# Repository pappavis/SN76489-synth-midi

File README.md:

Educatieve DIY USB-MIDI synthesizer gebaseerd op de SN76489 PSG,
aangestuurd via een ESP32-C2 met CircuitPython en een PCF8574
(I2C → parallel).

# Functionele specificaties  

## Ontwerpfilosofie
- Eerst breadboard, dan PCB
- Alles meetbaar met scope en multimeter
- Geen SMD-componenten
- Focus op leerbaarheid en reproduceerbaarheid

## Signaalpad (verplicht)
ESP32-C2 (USB MIDI)
→ PCF8574
→ SN76489
→ analoge filtering
→ variabel mono volume
→ audio-versterker
→ 3.5 mm TRS koptelefoon (dual-mono)

## Projectstatus
- [x] Stap 1 – Functionele specificaties
- [ ] Stap 2 – Technische specificaties
- [ ] Stap 3 – Blokdiagram
- [ ] Stap 4 – Breadboard ontwerp
- [ ] Stap 5 – Audio-versterker evaluatie
- [ ] Stap 6 – KiCad schema & PCB
- [ ] Stap 7 – Firmware architectuur
- [ ] Stap 8 – Test & debug
- [ ] Stap 9 – Verbeteringen

➡️ Begin bij `docs/01-functional-spec.md`
sn76489-midi-synth/
├── README.md
├── docs/
│   ├── 01-functional-spec.md
│   ├── 02-technical-spec.md
│   ├── 03-block-diagram.md
│   ├── 04-breadboard-design.md
│   ├── 05-audio-options-evaluation.md
│   ├── 06-kicad-design.md
│   ├── 07-firmware-architecture.md
│   ├── 08-test-and-debug.md
│   └── 09-improvements-and-next-steps.md
├── hardware/
│   ├── breadboard/
│   └── pcb/
├── firmware/
│   ├── circuitpython/
│   └── tools/
└── media/
    ├── photos/
    └── scope-captures/

# Werk-in-uitvoering

## Functioneel schema

## Printplaat klaar voor China-produtie

# CREDITS
In een opwelling gemaakt op een koude Zaterdagmiddag.

Michiel Erasmus

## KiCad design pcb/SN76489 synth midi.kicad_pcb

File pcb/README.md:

# Werk-in-uitvoering

## Functioneel schema

## Printplaat klaar voor China-produtie

Open deze met KiCAD 8.01.

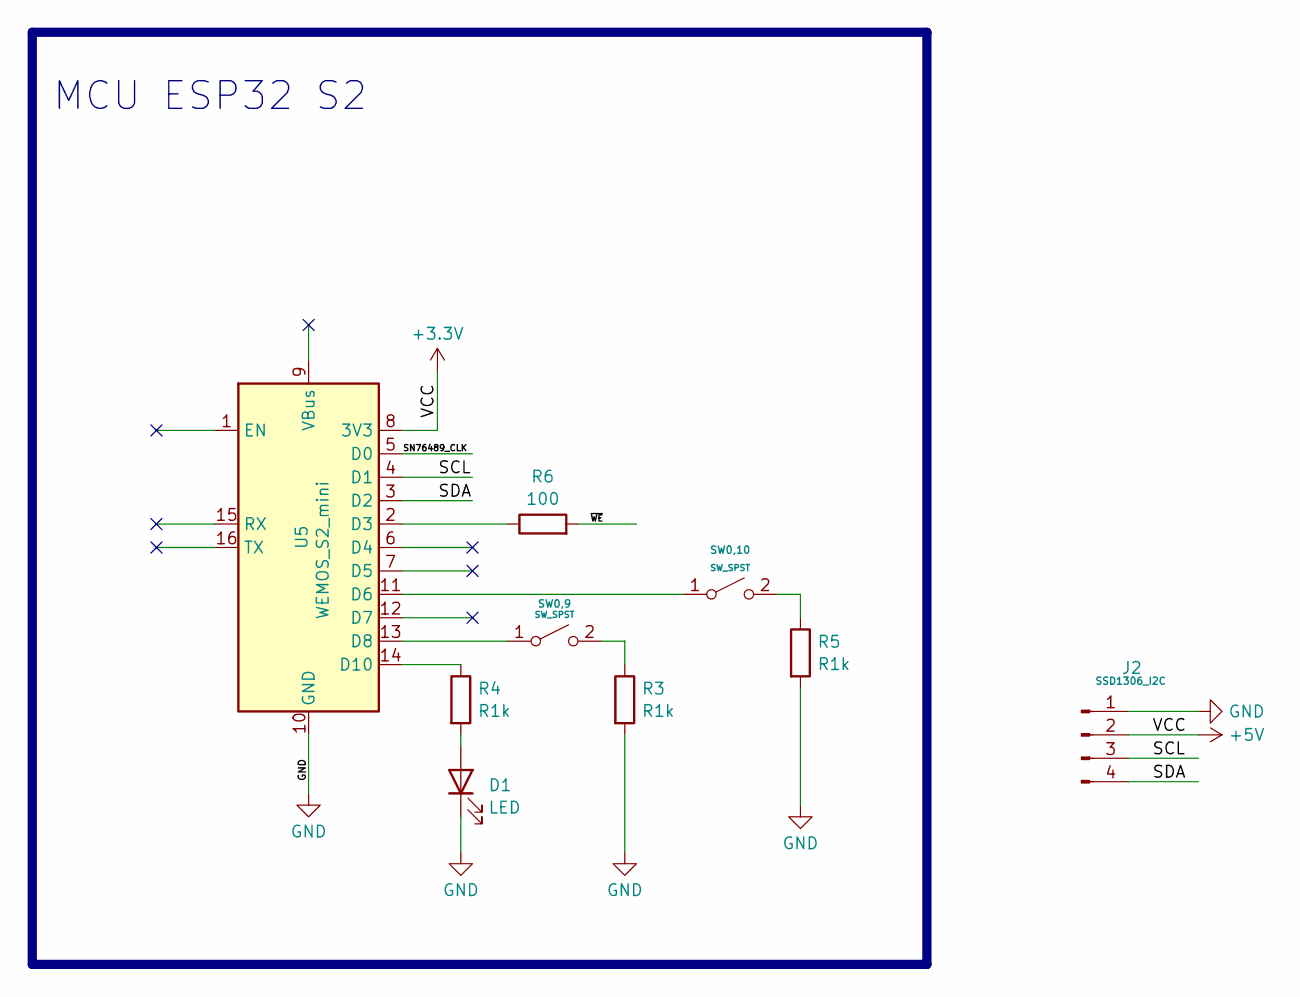
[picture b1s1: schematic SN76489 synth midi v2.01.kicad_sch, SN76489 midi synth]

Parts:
D1: LED; LED_D3.0mm
J2: SSD1306_I2C; Adafruit_SSD1306
R3, R4, R5: R1k; R_Axial_DIN0204_L3.6mm_D1.6mm_P7.62mm_Horizontal
R6: 100; R_Axial_DIN0204_L3.6mm_D1.6mm_P7.62mm_Horizontal
SW0,9, SW0,10: SW_SPST; KSA_Tactile_SPST
U5: WEMOS_S2_mini; WEMOS_C3_mini

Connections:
+3.3V: J2.2, U5.8 (3V3); also elsewhere on the board
/SCL: J2.3, U5.4 (D1); also elsewhere on the board
/SDA: J2.4, U5.3 (D2); also elsewhere on the board
/SN76489_CLK: U5.5 (D0); also elsewhere on the board
/~WE: R6.2; also elsewhere on the board
GND: D1.1 (K), J2.1, R3.2, R5.2, U5.10 (GND); also elsewhere on the board
unnamed: D1.2 (A), R4.2
unnamed: SW0,9.1 (A), U5.13 (D8)
unnamed: R3.1, SW0,9.2 (B)
unnamed: SW0,10.1 (A), U5.11 (D6)
unnamed: R5.1, SW0,10.2 (B)
unnamed: R6.1, U5.2 (D3)
unnamed: R4.1, U5.14 (D10)

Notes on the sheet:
MCU ESP32 S2

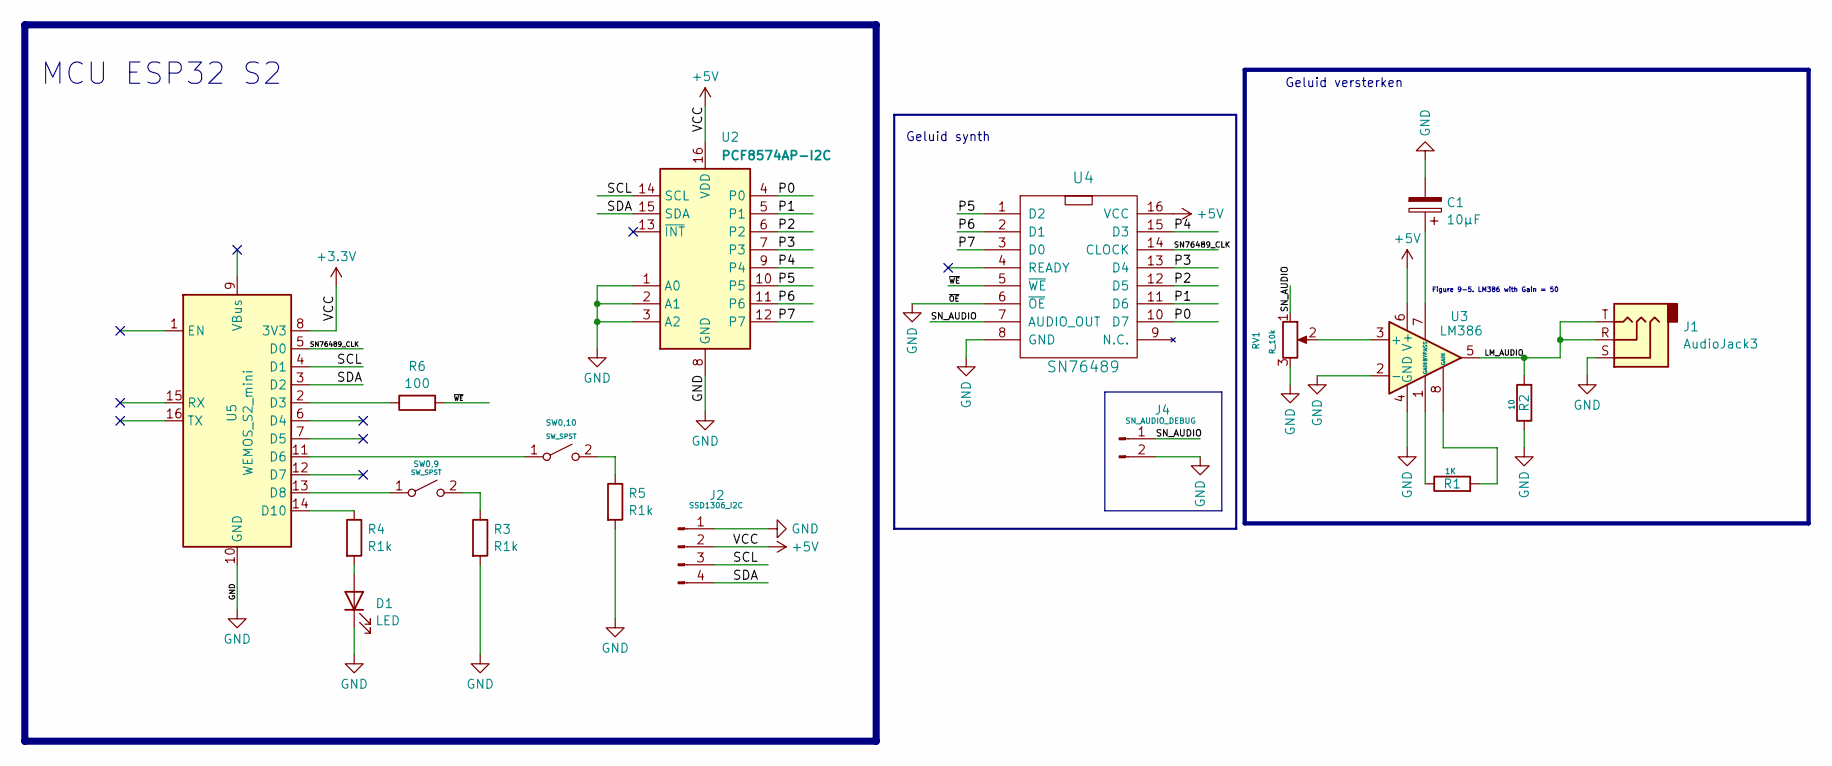
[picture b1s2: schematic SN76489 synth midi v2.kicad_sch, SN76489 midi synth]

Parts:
C1: 10µF; C_Radial_D6.3mm_H5.0mm_P2.50mm
D1: LED; LED_D3.0mm
J1: AudioJack3; Jack_3.5mm_CUI_SJ1-3515N_Horizontal
J2: SSD1306_I2C; Adafruit_SSD1306
J4: SN_AUDIO_DEBUG; PinHeader_1x02_P2.00mm_Vertical
R1: 1K; R_Axial_DIN0204_L3.6mm_D1.6mm_P7.62mm_Horizontal
R2: 10; R_Axial_DIN0204_L3.6mm_D1.6mm_P7.62mm_Horizontal
R3, R4, R5: R1k; R_Axial_DIN0204_L3.6mm_D1.6mm_P7.62mm_Horizontal
R6: 100; R_Axial_DIN0204_L3.6mm_D1.6mm_P7.62mm_Horizontal
RV1: R_10k; R_Axial_DIN0204_L3.6mm_D1.6mm_P7.62mm_Horizontal
SW0,9, SW0,10: SW_SPST; KSA_Tactile_SPST
U2: PCF8574AP-I2C; DIP-16_W7.62mm
U3: LM386; DIP-8_W7.62mm
U4: SN76489; DIP-16_W7.62mm
U5: WEMOS_S2_mini; WEMOS_C3_mini

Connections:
+3.3V: J2.2, U2.16 (VDD), U3.6 (V+), U4.16 (VCC), U5.8 (3V3)
/LM_AUDIO: J1.R, J1.T, R2.2, U3.5
/P0: U2.4 (P0), U4.10 (D7)
/P1: U2.5 (P1), U4.11 (D6)
/P2: U2.6 (P2), U4.12 (D5)
/P3: U2.7 (P3), U4.13 (D4)
/P4: U2.9 (P4), U4.15 (D3)
/P5: U2.10 (P5), U4.1 (D2)
/P6: U2.11 (P6), U4.2 (D1)
/P7: U2.12 (P7), U4.3 (D0)
/SCL: J2.3, U2.14 (SCL), U5.4 (D1)
/SDA: J2.4, U2.15 (SDA), U5.3 (D2)
/SN76489_CLK: U4.14 (CLOCK), U5.5 (D0)
/SN_AUDIO: J4.1, RV1.1, U4.7 (AUDIO_OUT)
/~WE: R6.2, U4.5 (~WE)
GND: C1.2, D1.1 (K), J1.S, J2.1, J4.2, R2.1, R3.2, R5.2, RV1.3, U2.1 (A0), U2.2 (A1), U2.3 (A2), U2.8 (GND), U3.2 (-), U3.4 (GND), U4.6 (~OE), U4.8 (GND), U5.10 (GND)
unnamed: D1.2 (A), R4.2
unnamed: R1.1, U3.1 (GAIN)
unnamed: R1.2, U3.8 (GAIN)
unnamed: SW0,9.1 (A), U5.13 (D8)
unnamed: R3.1, SW0,9.2 (B)
unnamed: SW0,10.1 (A), U5.11 (D6)
unnamed: R5.1, SW0,10.2 (B)
unnamed: RV1.2, U3.3 (+)
unnamed: C1.1, U3.7 (BYPASS)
unnamed: R6.1, U5.2 (D3)
unnamed: R4.1, U5.14 (D10)

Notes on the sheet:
Geluid versterken
Figure 9-5. LM386 with Gain = 50
MCU ESP32 S2
Geluid synth

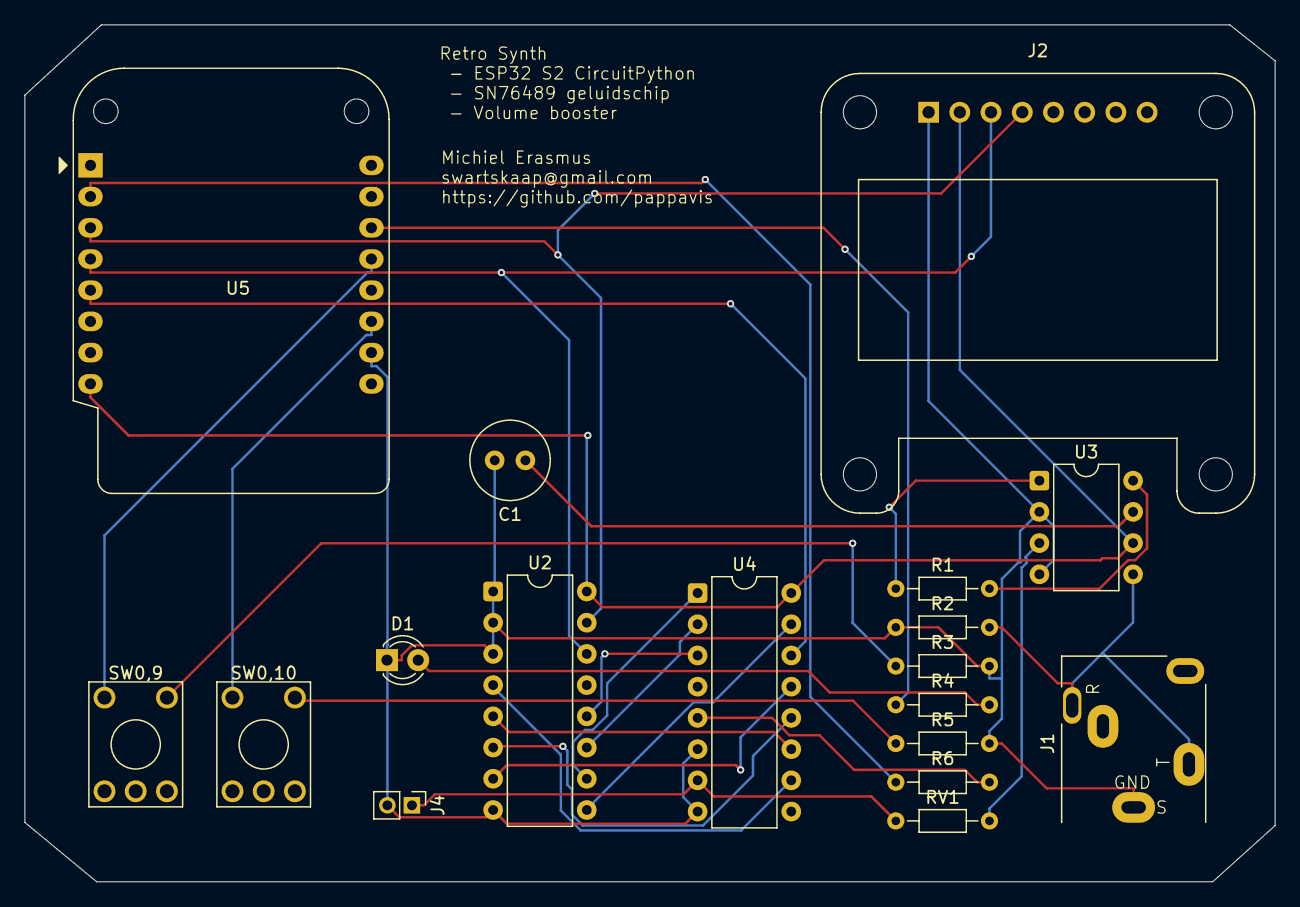
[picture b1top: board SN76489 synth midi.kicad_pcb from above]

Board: 2 copper layers, 101.7 x 69.7 mm, 18 parts (0 on the bottom side), 27 nets.

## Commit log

2026-01-11 0.01 UNTESTED version.. need to breadboard it
2026-01-18 0.01 PCB versie
2026-02-02 v0.05: add 3-voice allocation per chip, ADSR-lite via volume writes, pitch bend; new --test chords/--test sweep
2026-02-02 v0.06: VGM playback stable (path/list/loop/speed) with counters; keep MIDI+tests
